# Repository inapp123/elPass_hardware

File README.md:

# ePass EL or elPass

**An open-source EL display controller built on the Xilinx Zynq-7010.**

ePass EL drives an electroluminescent (EL) panel from a Zynq-7010 SoC, pairing
PS-side Linux with PL-side panel timing so you get a real compositor on top of a
display technology that usually only sees bit-banged microcontroller drivers.
HDMI in/out, WiFi/BT, USB host, a resistive touchscreen, and USB-C PD power all
live on a single self-designed four-layer board.

> Rhodes Island Engineering Dept. (c) 1097 — *because every ruler needs a screen.*

---

## Status

| Subsystem            | State                                                        |
| -------------------- | ------------------------------------------------------------ |
| PCB (4-layer)        | **Fabricated and bring-up tested.** Working hardware.        |
| FPGA / Linux         | Architecture defined; EL driver + DRM compositor in progress |
| Enclosure            | 2-piece FDM/resin shell, parametric (build123d), in design   |

This is `Rev 1`. KiCad 10.0.3 source, schematic dated 2026-05-25.

PCB is designed for JLC04016-3313 stack.1.6mm,3313 imdepend matching.

---

## Highlights

- **Zynq-7010 (CLG400)** — dual-core Cortex-A9 PS + Artix-class PL on one die.
- **EL panel driver in the PL** — column/row drive (`UD*`/`LD*`/`CP*`/`S`) with
  1-bit temporal dithering, level-shifted to the panel through dual TXS0108E.
- **DRM/KMS on Linux** — a single-master compositor owns the CRTC; clients hand
  in buffers over dmabuf. Legacy fbdev programs and even an X server can run as
  clients without ever touching the real DRM master.
- **HDMI, both directions** — J2 is a dual-mode sink/source. Default build is a
  sink (TMDS receive into HR banks via IDELAY/ISERDES); populate `D2` to flip it
  into a source.
- **WiFi + Bluetooth** — RTL8723BS over SDIO (routed through EMIO to the PL),
  with a 2.4 GHz chip antenna and a proper RF keepout.
- **USB-C PD power** — CH224K negotiates 12 V for the panel rail; data lines
  stay free for whatever you want.
- **USB 2.0 host** — USB3320 ULPI PHY (24 MHz) to a full-size Type-A port.
- **Resistive touch** — XPT2046 over SPI.
- **microSD** boot + storage, RTC-less but with the usual JTAG/UART debug paths.

---

## Architecture

```mermaid
flowchart TB
    USBC[USB-C In<br/>CH224K PD sink] --> PWR
    PWR[EA3059 quad buck<br/>+ TPS563201] -->|1V0 / 1V8 / 1V35 / 3V3 / 5V / 12V| ZYNQ

    subgraph ZYNQ[Zynq-7010]
        PS[PS<br/>Cortex-A9 + Linux]
        PL[PL<br/>EL timing + dither<br/>HDMI TMDS]
    end

    PS <-->|EMIO SDIO| WIFI[RTL8723BS<br/>WiFi/BT]
    PS --> USB[USB3320 ULPI] --> USBA[USB-A Host]
    PS --> SD[microSD]
    PS <-->|DDR| DDR[MT41K256M16<br/>512 MB DDR3L]

    PL -->|level shift| EL[EL Panel]
    PL <--> HDMI[HDMI A<br/>sink / source]
    PS -->|SPI| TOUCH[XPT2046<br/>resistive touch]
```

### PS / PL split

- **PS** runs Linux and owns the slow-and-smart side: USB, SD, the RTL8723BS
  (SDIO bridged out through EMIO to PL pins), DDR3L, and the touch SPI link.
- **PL** owns the timing-critical side: generating EL panel drive waveforms with
  1-bit dithering, and the HDMI TMDS datapath.

---

## Power tree

USB-C comes in, CH224K trips the source to **12 V**, and everything fans out from
there. The Zynq rails are brought up in the order the datasheet asks for.

| Rail   | Source       | Notes                                  |
| ------ | ------------ | -------------------------------------- |
| +5 V   | TPS563201    | Buck from VBUS                         |
| +1.0 V | EA3059       | `VCCINT` / `VCCPINT`                    |
| +1.8 V | EA3059       | `VCCAUX` / `VCCPAUX` / MIO bank 1       |
| +1.35 V| EA3059       | DDR3L `VCCO_DDR`                        |
| +3.3 V | EA3059       | I/O banks, MIO bank 0, last to rise    |

**Sequence:** `1.0 V → 1.8 V → 1.35 V → 3.3 V`
(approx. instant → 22 ms → 41 ms → 55 ms, set by the enable-cap timing).
A **MAX811** supervises the last-rising 3.3 V rail and drives `PS_POR_B`.

**Panel budget:** 5 V @ 300 mA max, 12 V @ 1.3 A max.

---

## Boot configuration

Mode straps live on the MIO pins (see `zynq_misc`):

| Pins      | Value      | Meaning                                   |
| --------- | ---------- | ----------------------------------------- |
| MIO[6]    | `0`        | Wait for PLL lock, then run BootROM       |
| MIO[8:7]  | `2'b10`    | 3.3 V on both MIO banks                    |
| MIO[5:3]  | `3'b110`   | Boot from SD card                          |
| MIO[2]    | `0`        | JTAG chain: cascaded                       |

PS reference clock is a 50 MHz oscillator. JTAG is broken out on a ZX-SH1.0
header for bring-up.

---

## Software stack

The interesting part isn't that it runs Linux — it's *how the display is shared.*

- **Single-master DRM compositor.** A DRM lease can't split a CRTC between two
  masters, so one compositor owns all atomic commits. Clients submit buffers as
  dmabuf file descriptors passed over a Unix socket (`SCM_RIGHTS`).
- **Legacy fbdev support** via `LD_PRELOAD`, intercepting `open`/`ioctl`/`mmap`
  so old framebuffer programs think they own a screen.
- **X11 as a client** — `xf86-video-fbdev` runs against the compositor's virtual
  framebuffer, keeping the compositor as the sole DRM master.
- **Touch routing.** The real input device is grabbed (`EVIOCGRAB`) and a virtual
  device is published via `uinput`/`libevdev`; the compositor routes events by
  overlay visibility. On focus switch, in-flight multitouch slots are cancelled
  cleanly (`ABS_MT_TRACKING_ID = -1`, `BTN_TOUCH = 0`, `SYN_REPORT`). A udev rule
  (`LIBINPUT_IGNORE_DEVICE=1`) hides the raw device from X's libinput.

## Credits

This design stands on the shoulders of:

- **ZYNQ_Ruler** by Stanlazy — <https://github.com/Stanlazy/ZYNQ_Ruler>
- **Enchanter** by Modos Tech / Wenting Zhang
- **EBAZ4205** community reverse-engineering work

Thanks to everyone who documented Zynq-7010 minimal designs and EL driving so the
rest of us didn't have to start from a blank schematic.

---

## License

CERN-OHL-P.

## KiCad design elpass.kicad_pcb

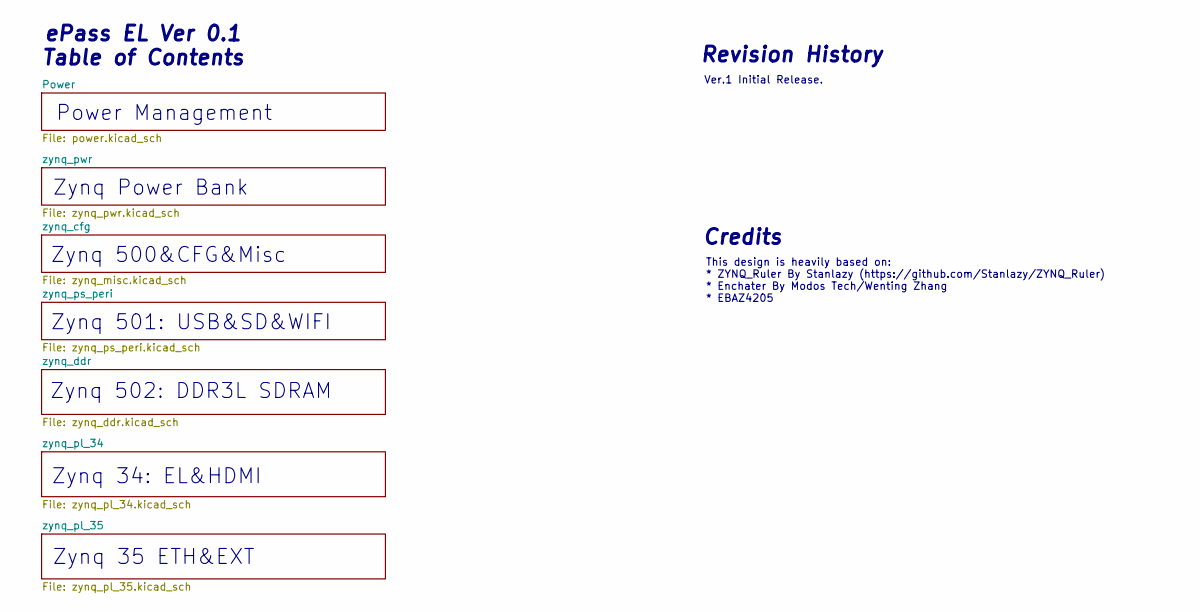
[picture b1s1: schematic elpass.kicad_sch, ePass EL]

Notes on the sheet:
Zynq Power Bank
Zynq 502: DDR3L SDRAM
Zynq 35 ETH&EXT
ePass EL Ver 0.1 Table of Contents
Power Management
Credits
Zynq 500&CFG&Misc
Zynq 34: EL&HDMI
Ver.1 Initial Release.
Zynq 501: USB&SD&WIFI
This design is heavily based on: * ZYNQ_Ruler By Stanlazy (https://github.com/Stanlazy/ZYNQ_Ruler) * Enchater By Modos Tech/Wenting Zhang * EBAZ4205
Revision History

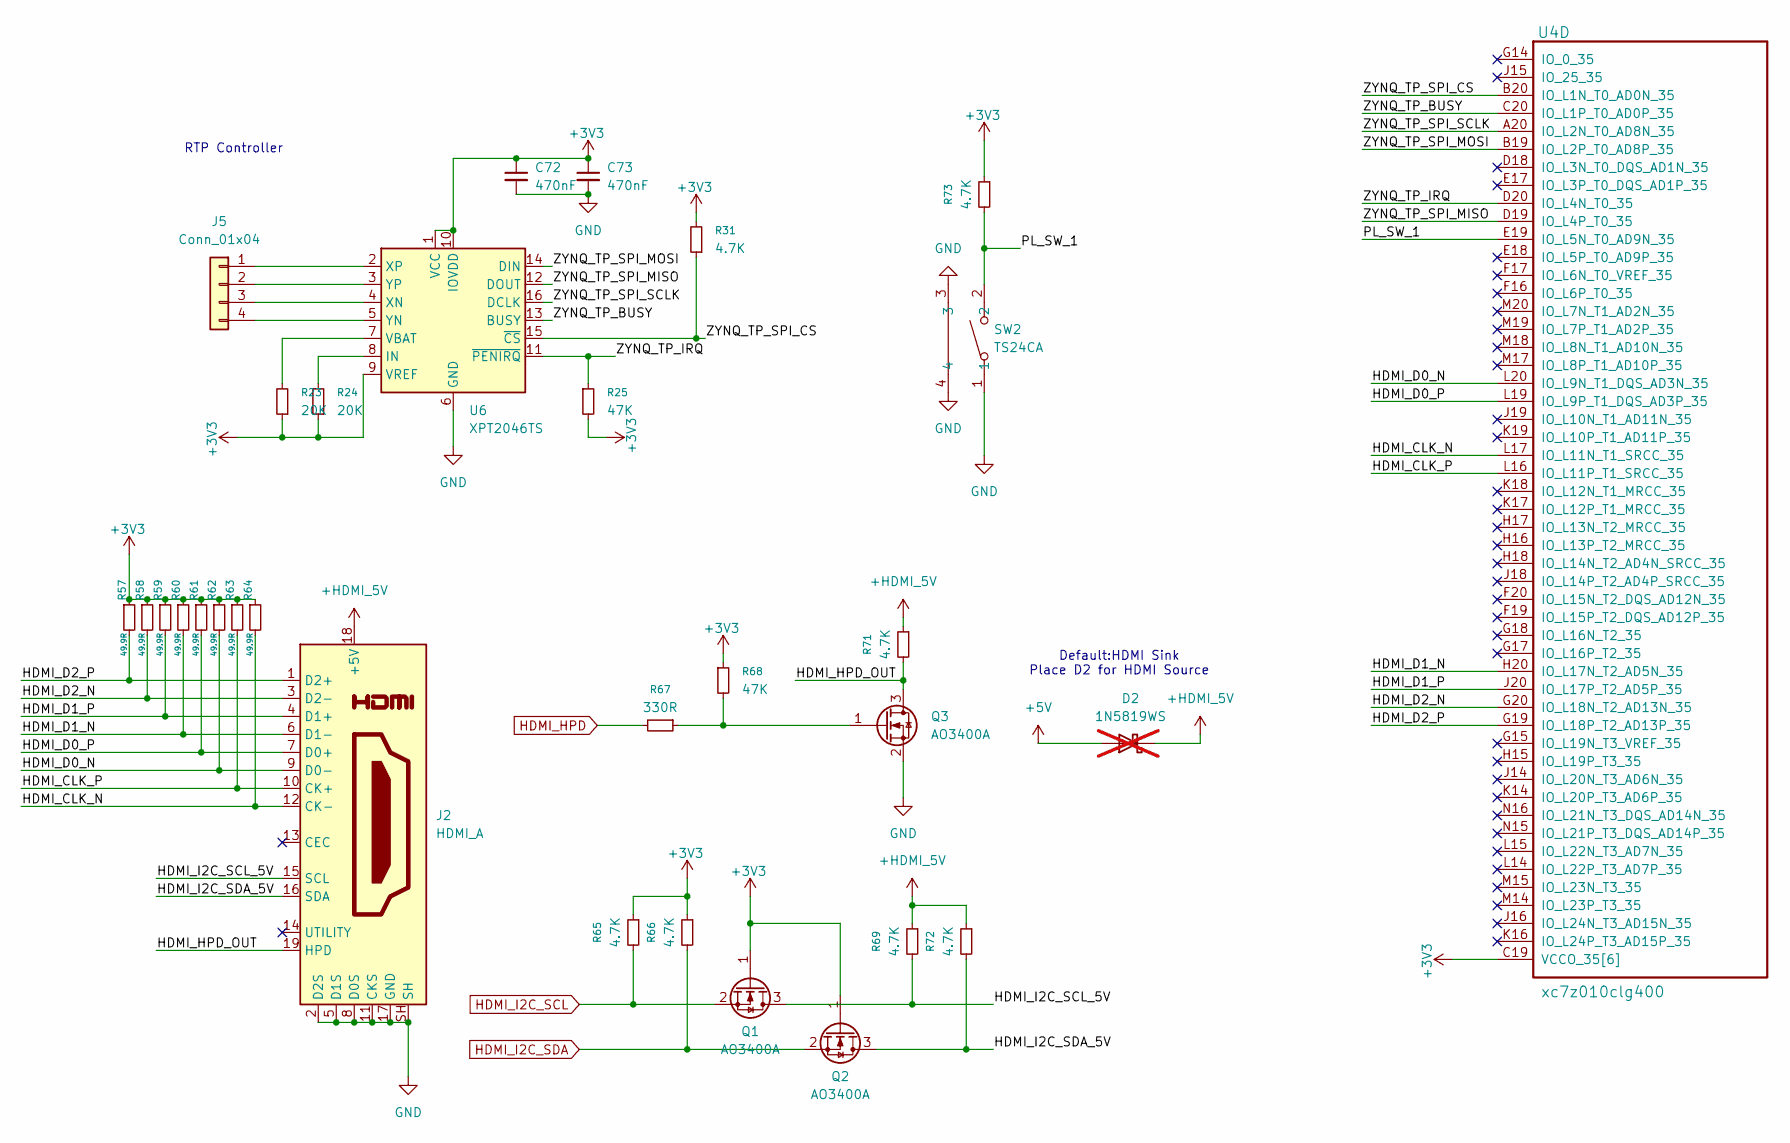
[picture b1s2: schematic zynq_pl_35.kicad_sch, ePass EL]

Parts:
C72, C73: 470nF; C_0201_0603Metric
D2: 1N5819WS; D_SOD-323; not fitted
J2: HDMI_A; HDMI_A_Molex_208658-1001_Horizontal
J5: Conn_01x04; PinHeader_1x04_P2.54mm_Horizontal
Q1, Q2, Q3: AO3400A; SOT-23
R23, R24: 20K; R_0402_1005Metric
R25, R68: 47K; R_0402_1005Metric
R31, R65, R66, R69, R71, R72, R73: 4.7K; R_0402_1005Metric
R57, R58, R59, R60, R61, R62, R63, R64: 49.9R; R_0402_1005Metric
R67: 330R; R_0402_1005Metric
SW2: TS24CA; SW-SMD_2P-TS24CA; MPN TS24CA; LCSC Part C393942
U4: xc7z010clg400; Xilinx_CLG400_NoPaste_JLC_Package_Delay
U6: XPT2046TS; TSSOP-16_4.4x5mm_P0.65mm

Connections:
+3V3: C72.1, C73.1, Q1.1 (G), Q2.1 (G), R23.1, R24.1, R25.2, R31.2, R57.1, R58.1, R59.1, R60.1, R61.1, R62.1, R63.1, R64.1, R65.1, R66.1, R68.1, R73.1, U4.C19 (VCCO_35[6]), U4.F18 (VCCO_35[6]), U4.H14 (VCCO_35[6]), U4.J17 (VCCO_35[6]), U4.K20 (VCCO_35[6]), U4.M16 (VCCO_35[6]), U6.1 (VCC), U6.9 (VREF), U6.10 (IOVDD); also elsewhere on the board
+5V: D2.2 (A); also elsewhere on the board
+HDMI_5V: D2.1 (K), J2.18 (+5V), R69.1, R71.1, R72.1
/zynq_pl_35/HDMI_CLK_N: J2.12 (CK-), R64.2, U4.L17 (IO_L11N_T1_SRCC_35)
/zynq_pl_35/HDMI_CLK_P: J2.10 (CK+), R63.2, U4.L16 (IO_L11P_T1_SRCC_35)
/zynq_pl_35/HDMI_D0_N: J2.9 (D0-), R62.2, U4.L20 (IO_L9N_T1_DQS_AD3N_35)
/zynq_pl_35/HDMI_D0_P: J2.7 (D0+), R61.2, U4.L19 (IO_L9P_T1_DQS_AD3P_35)
/zynq_pl_35/HDMI_D1_N: J2.6 (D1-), R60.2, U4.H20 (IO_L17N_T2_AD5N_35)
/zynq_pl_35/HDMI_D1_P: J2.4 (D1+), R59.2, U4.J20 (IO_L17P_T2_AD5P_35)
/zynq_pl_35/HDMI_D2_N: J2.3 (D2-), R58.2, U4.G20 (IO_L18N_T2_AD13N_35)
/zynq_pl_35/HDMI_D2_P: J2.1 (D2+), R57.2, U4.G19 (IO_L18P_T2_AD13P_35)
/zynq_pl_35/HDMI_HPD_OUT: J2.19 (HPD), Q3.3 (D), R71.2
/zynq_pl_35/HDMI_I2C_SCL_5V: J2.15 (SCL), Q1.3 (D), R69.2
/zynq_pl_35/HDMI_I2C_SDA_5V: J2.16 (SDA), Q2.3 (D), R72.2
/zynq_pl_35/PL_SW_1: R73.2, SW2.2, U4.E19 (IO_L5N_T0_AD9N_35)
/zynq_pl_35/ZYNQ_TP_BUSY: U4.C20 (IO_L1P_T0_AD0P_35), U6.13 (BUSY)
/zynq_pl_35/ZYNQ_TP_IRQ: R25.1, U4.D20 (IO_L4N_T0_35), U6.11 (~PENIRQ)
/zynq_pl_35/ZYNQ_TP_SPI_CS: R31.1, U4.B20 (IO_L1N_T0_AD0N_35), U6.15 (~CS)
/zynq_pl_35/ZYNQ_TP_SPI_MISO: U4.D19 (IO_L4P_T0_35), U6.12 (DOUT)
/zynq_pl_35/ZYNQ_TP_SPI_MOSI: U4.B19 (IO_L2P_T0_AD8P_35), U6.14 (DIN)
/zynq_pl_35/ZYNQ_TP_SPI_SCLK: U4.A20 (IO_L2N_T0_AD8N_35), U6.16 (DCLK)
GND: C72.2, C73.2, J2.2 (D2S), J2.5 (D1S), J2.8 (D0S), J2.11 (CKS), J2.17 (GND), J2.SH, Q3.2 (S), SW2.1, SW2.3, SW2.4, U6.6 (GND); also elsewhere on the board
HDMI_HPD: R67.2; also elsewhere on the board
HDMI_I2C_SCL: Q1.2 (S), R65.2; also elsewhere on the board
HDMI_I2C_SDA: Q2.2 (S), R66.2; also elsewhere on the board
unnamed: J5.1, U6.2 (XP)
unnamed: J5.2, U6.3 (YP)
unnamed: J5.3, U6.4 (XN)
unnamed: J5.4, U6.5 (YN)
unnamed: Q3.1 (G), R67.1, R68.2
unnamed: R24.2, U6.8 (IN)
unnamed: R23.2, U6.7 (VBAT)

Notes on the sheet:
Default:HDMI Sink Place D2 for HDMI Source
RTP Controller

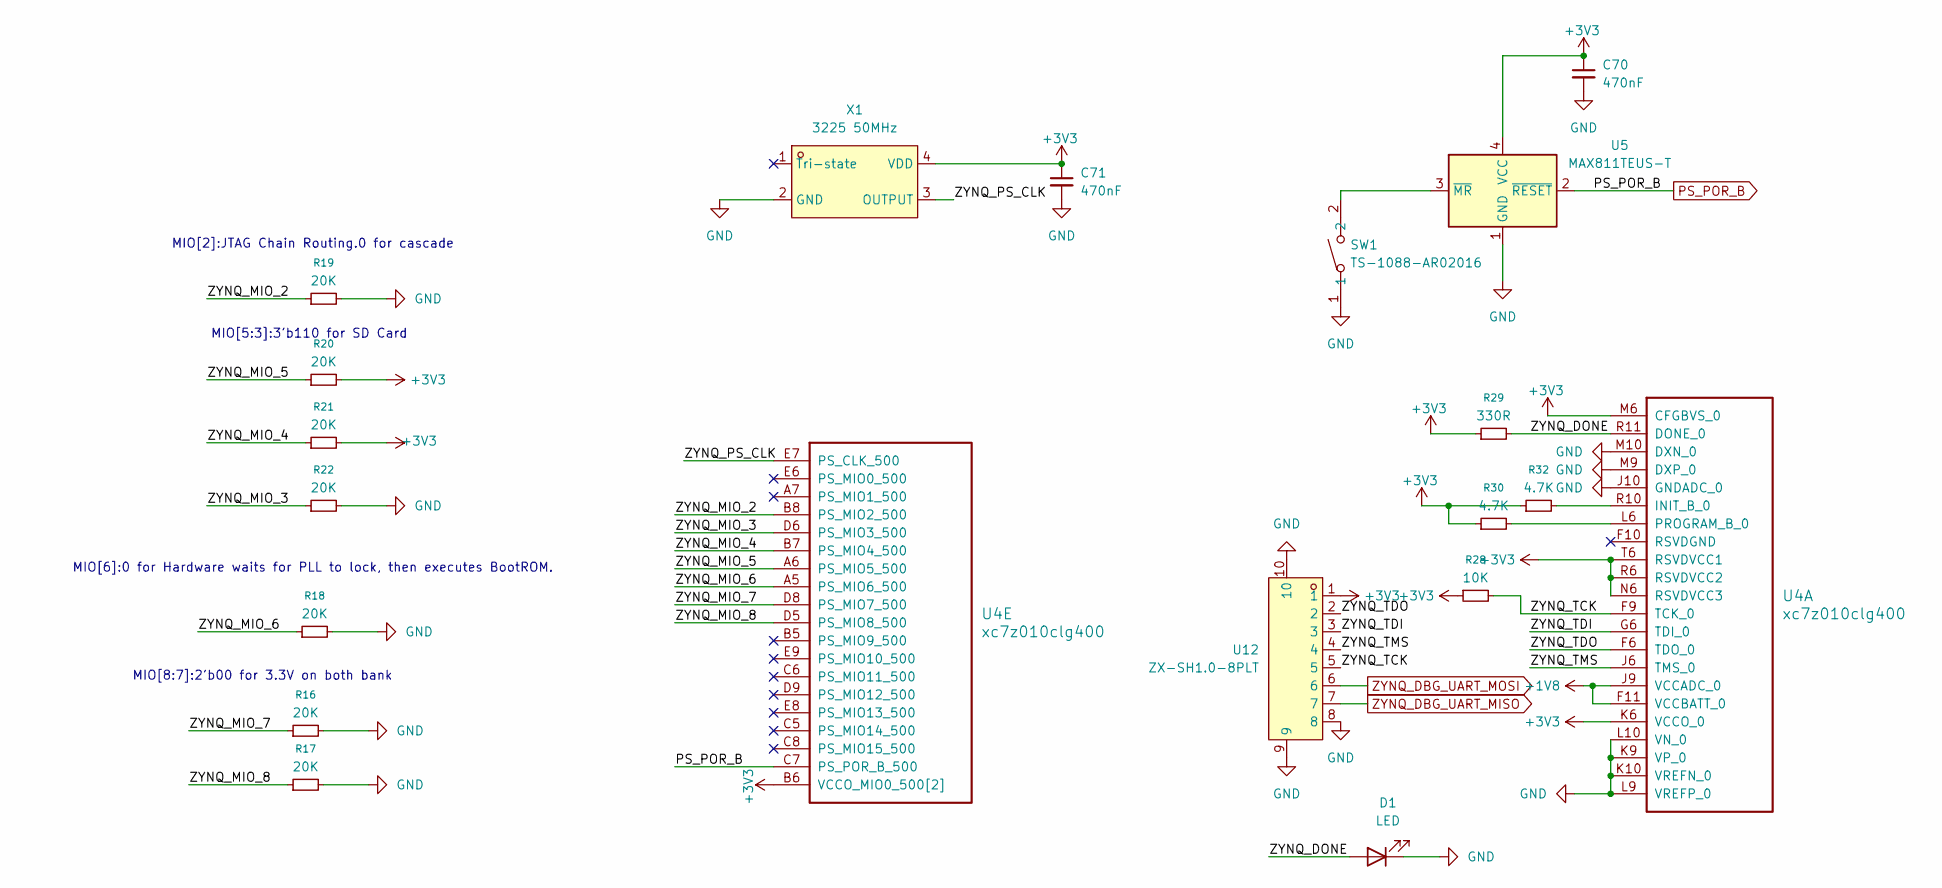
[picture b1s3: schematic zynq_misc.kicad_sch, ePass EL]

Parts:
C70, C71: 470nF; C_0201_0603Metric
D1: LED; LED_0603_1608Metric
R16, R17, R18, R19, R20, R21, R22: 20K; R_0402_1005Metric
R28: 10K; R_0402_1005Metric
R29: 330R; R_0402_1005Metric
R30, R32: 4.7K; R_0402_1005Metric
SW1: TS-1088-AR02016; SW-SMD_L3.9-W3.0-P4.45; MPN TS-1088-AR02016; LCSC Part C720477
U4: xc7z010clg400; Xilinx_CLG400_NoPaste_JLC_Package_Delay
U5: MAX811TEUS-T; SOT-143
U12: ZX-SH1.0-8PLT; CONN-SMD_8P-P1.00_MEGASTAR_ZX-SH1.0-8PLT; MPN ZX-SH1.0-8PLT; LCSC Part C7430457
X1: 3225 50MHz; OSC-SMD_4P-L3.2-W2.5-BL; MPN OT322550MJBA4SL; LCSC Part C717684

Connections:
+1V8: U4.F11 (VCCBATT_0), U4.J9 (VCCADC_0); also elsewhere on the board
+3V3: C70.1, C71.1, R20.2, R21.2, R28.1, R29.1, R30.1, R32.1, U4.B6 (VCCO_MIO0_500[2]), U4.D7 (VCCO_MIO0_500[2]), U4.K6 (VCCO_0), U4.M6 (CFGBVS_0), U4.N6 (RSVDVCC3), U4.R6 (RSVDVCC2), U4.T6 (RSVDVCC1), U5.4 (VCC), U12.1, X1.4 (VDD); also elsewhere on the board
/zynq_cfg/ZYNQ_DONE: D1.2 (A), R29.2, U4.R11 (DONE_0)
/zynq_cfg/ZYNQ_MIO_2: R19.1, U4.B8 (PS_MIO2_500)
/zynq_cfg/ZYNQ_MIO_3: R22.1, U4.D6 (PS_MIO3_500)
/zynq_cfg/ZYNQ_MIO_4: R21.1, U4.B7 (PS_MIO4_500)
/zynq_cfg/ZYNQ_MIO_5: R20.1, U4.A6 (PS_MIO5_500)
/zynq_cfg/ZYNQ_MIO_6: R18.1, U4.A5 (PS_MIO6_500)
/zynq_cfg/ZYNQ_MIO_7: R16.1, U4.D8 (PS_MIO7_500)
/zynq_cfg/ZYNQ_MIO_8: R17.1, U4.D5 (PS_MIO8_500)
/zynq_cfg/ZYNQ_PS_CLK: U4.E7 (PS_CLK_500), X1.3 (OUTPUT)
/zynq_cfg/ZYNQ_TCK: R28.2, U4.F9 (TCK_0), U12.5
/zynq_cfg/ZYNQ_TDI: U4.G6 (TDI_0), U12.3
/zynq_cfg/ZYNQ_TDO: U4.F6 (TDO_0), U12.2
/zynq_cfg/ZYNQ_TMS: U4.J6 (TMS_0), U12.4
GND: C70.2, C71.2, D1.1 (K), R16.2, R17.2, R18.2, R19.2, R22.2, SW1.1, U4.J10 (GNDADC_0), U4.K9 (VP_0), U4.K10 (VREFN_0), U4.L9 (VREFP_0), U4.L10 (VN_0), U4.M9 (DXP_0), U4.M10 (DXN_0), U5.1 (GND), U12.8, U12.9, U12.10, X1.2 (GND); also elsewhere on the board
unnamed: R32.2, U4.R10 (INIT_B_0)
unnamed: R30.2, U4.L6 (PROGRAM_B_0)
unnamed: SW1.2, U5.3 (~MR)
PS_POR_B: U4.C7 (PS_POR_B_500), U5.2 (~RESET)
ZYNQ_DBG_UART_MISO: U12.7; also elsewhere on the board
ZYNQ_DBG_UART_MOSI: U12.6; also elsewhere on the board

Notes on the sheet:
MIO[5:3]:3'b110 for SD Card
MIO[8:7]:2'b00 for 3.3V on both bank
MIO[2]:JTAG Chain Routing.0 for cascade
MIO[6]:0 for Hardware waits for PLL to lock, then executes BootROM.

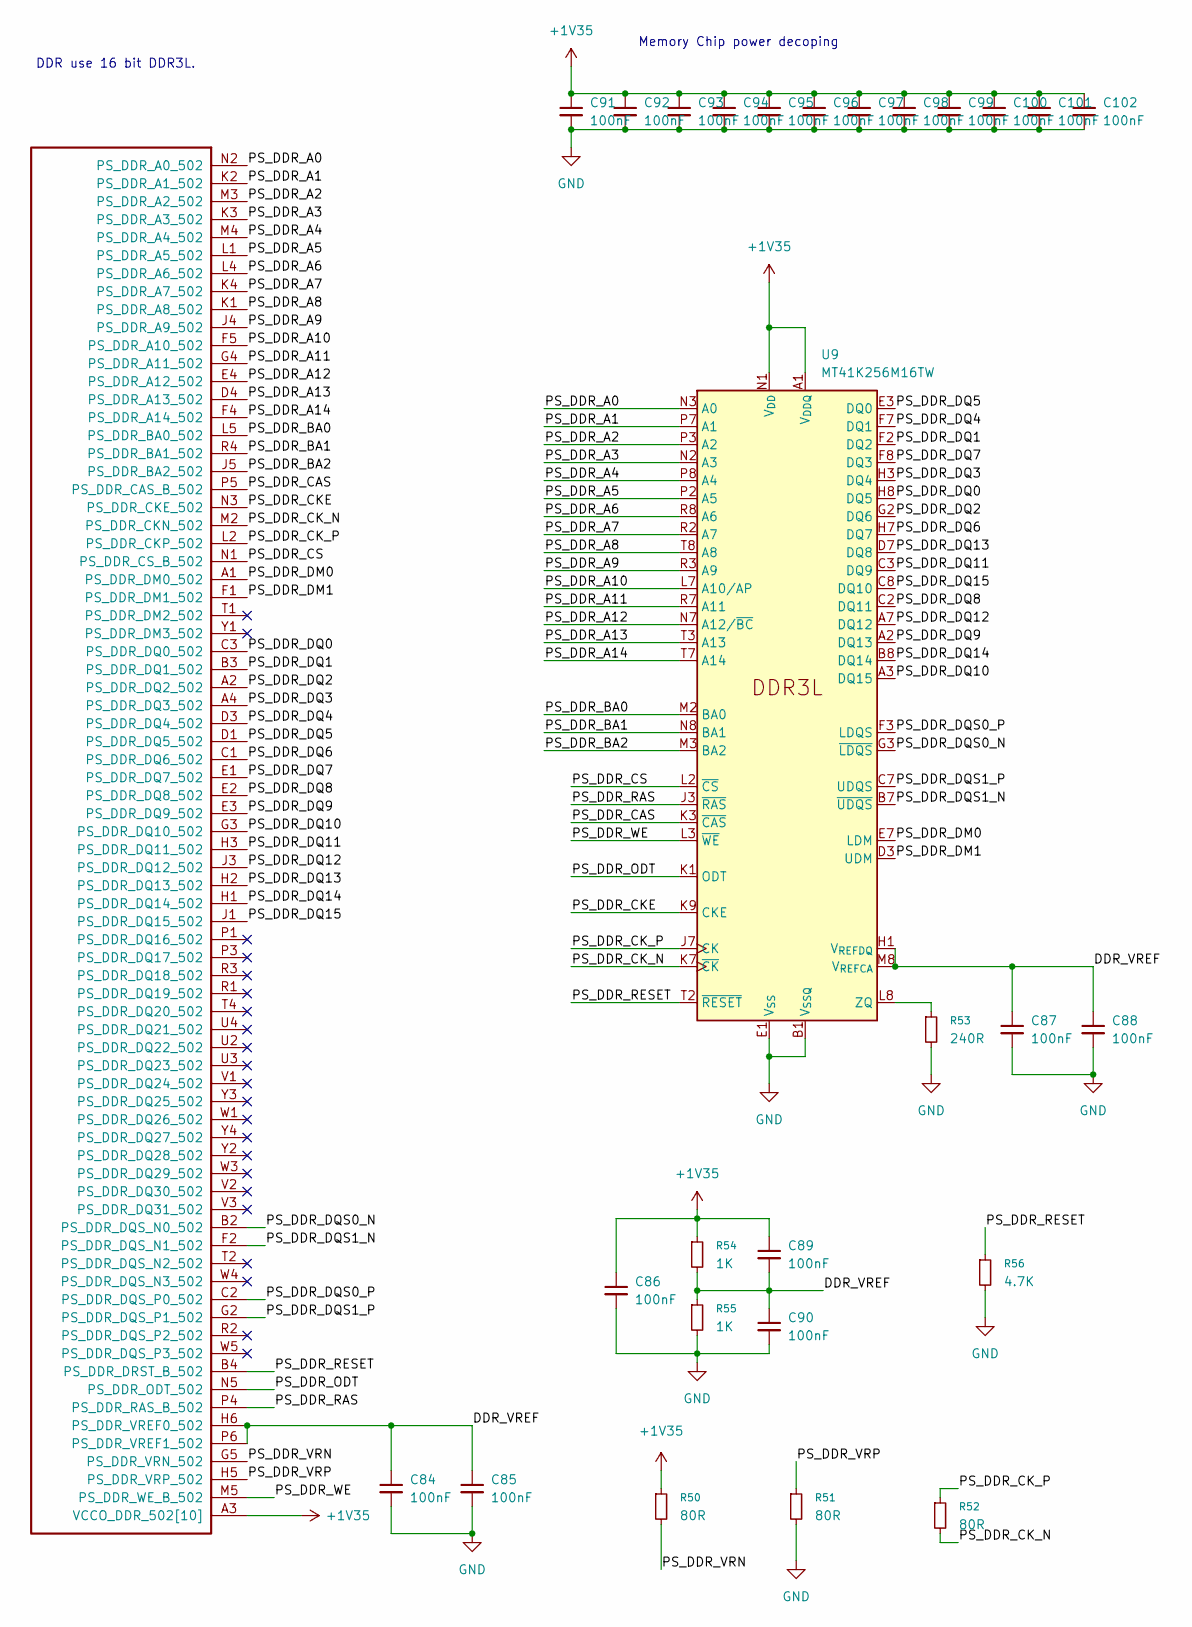
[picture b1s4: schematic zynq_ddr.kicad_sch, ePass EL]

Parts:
C84, C86, C87, C88, C89, C90, C91, C92, C93, C94, C95, C98, C99, C100, C101, C102: 100nF; C_0201_0603Metric
C85, C96, C97: 100nF; C_0201_0603Metric_WideGap
R50, R51: 80R; R_0201_0603Metric
R52: 80R; C_0201_0603Metric_WideGap
R53: 240R; R_0201_0603Metric
R54, R55: 1K; R_0402_1005Metric
R56: 4.7K; R_0402_1005Metric
U4: xc7z010clg400; Xilinx_CLG400_NoPaste_JLC_Package_Delay
U9: MT41K256M16TW; BGA-96_P0.8mm_NoPaste

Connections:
+1V35: C86.1, C89.1, C91.1, C92.1, C93.1, C94.1, C95.1, C96.1, C97.1, C98.1, C99.1, C100.1, C101.1, C102.1, R50.1, R54.1, U4.A3 (VCCO_DDR_502[10]), U4.D2 (VCCO_DDR_502[10]), U4.E5 (VCCO_DDR_502[10]), U4.G1 (VCCO_DDR_502[10]), U4.H4 (VCCO_DDR_502[10]), U4.L3 (VCCO_DDR_502[10]), U4.P2 (VCCO_DDR_502[10]), U4.R5 (VCCO_DDR_502[10]), U4.U1 (VCCO_DDR_502[10]), U4.V4 (VCCO_DDR_502[10]), U9.A1 (V_{DDQ}), U9.A8 (V_{DDQ}), U9.B2 (V_{DD}), U9.C1 (V_{DDQ}), U9.C9 (V_{DDQ}), U9.D2 (V_{DDQ}), U9.D9 (V_{DD}), U9.E9 (V_{DDQ}), U9.F1 (V_{DDQ}), U9.G7 (V_{DD}), U9.H2 (V_{DDQ}), U9.H9 (V_{DDQ}), U9.K2 (V_{DD}), U9.K8 (V_{DD}), U9.N1 (V_{DD}), U9.N9 (V_{DD}), U9.R1 (V_{DD}), U9.R9 (V_{DD}); also elsewhere on the board
/zynq_ddr/DDR_VREF: C84.1, C85.1, C87.1, C88.1, C89.2, C90.1, R54.2, R55.1, U4.H6 (PS_DDR_VREF0_502), U4.P6 (PS_DDR_VREF1_502), U9.H1 (V_{REFDQ}), U9.M8 (V_{REFCA})
/zynq_ddr/PS_DDR_A0: U4.N2 (PS_DDR_A0_502), U9.N3 (A0)
/zynq_ddr/PS_DDR_A1: U4.K2 (PS_DDR_A1_502), U9.P7 (A1)
/zynq_ddr/PS_DDR_A2: U4.M3 (PS_DDR_A2_502), U9.P3 (A2)
/zynq_ddr/PS_DDR_A3: U4.K3 (PS_DDR_A3_502), U9.N2 (A3)
/zynq_ddr/PS_DDR_A4: U4.M4 (PS_DDR_A4_502), U9.P8 (A4)
/zynq_ddr/PS_DDR_A5: U4.L1 (PS_DDR_A5_502), U9.P2 (A5)
/zynq_ddr/PS_DDR_A6: U4.L4 (PS_DDR_A6_502), U9.R8 (A6)
/zynq_ddr/PS_DDR_A7: U4.K4 (PS_DDR_A7_502), U9.R2 (A7)
/zynq_ddr/PS_DDR_A8: U4.K1 (PS_DDR_A8_502), U9.T8 (A8)
/zynq_ddr/PS_DDR_A9: U4.J4 (PS_DDR_A9_502), U9.R3 (A9)
/zynq_ddr/PS_DDR_A10: U4.F5 (PS_DDR_A10_502), U9.L7 (A10/AP)
/zynq_ddr/PS_DDR_A11: U4.G4 (PS_DDR_A11_502), U9.R7 (A11)
/zynq_ddr/PS_DDR_A12: U4.E4 (PS_DDR_A12_502), U9.N7 (A12/~BC)
/zynq_ddr/PS_DDR_A13: U4.D4 (PS_DDR_A13_502), U9.T3 (A13)
/zynq_ddr/PS_DDR_A14: U4.F4 (PS_DDR_A14_502), U9.T7 (A14)
/zynq_ddr/PS_DDR_BA0: U4.L5 (PS_DDR_BA0_502), U9.M2 (BA0)
/zynq_ddr/PS_DDR_BA1: U4.R4 (PS_DDR_BA1_502), U9.N8 (BA1)
/zynq_ddr/PS_DDR_BA2: U4.J5 (PS_DDR_BA2_502), U9.M3 (BA2)
/zynq_ddr/PS_DDR_CAS: U4.P5 (PS_DDR_CAS_B_502), U9.K3 (~CAS)
/zynq_ddr/PS_DDR_CKE: U4.N3 (PS_DDR_CKE_502), U9.K9 (CKE)
/zynq_ddr/PS_DDR_CK_N: R52.2, U4.M2 (PS_DDR_CKN_502), U9.K7 (~CK)
/zynq_ddr/PS_DDR_CK_P: R52.1, U4.L2 (PS_DDR_CKP_502), U9.J7 (CK)
/zynq_ddr/PS_DDR_CS: U4.N1 (PS_DDR_CS_B_502), U9.L2 (~CS)
/zynq_ddr/PS_DDR_DM0: U4.A1 (PS_DDR_DM0_502), U9.E7 (LDM)
/zynq_ddr/PS_DDR_DM1: U4.F1 (PS_DDR_DM1_502), U9.D3 (UDM)
/zynq_ddr/PS_DDR_DQ0: U4.C3 (PS_DDR_DQ0_502), U9.H8 (DQ5)
/zynq_ddr/PS_DDR_DQ1: U4.B3 (PS_DDR_DQ1_502), U9.F2 (DQ2)
/zynq_ddr/PS_DDR_DQ2: U4.A2 (PS_DDR_DQ2_502), U9.G2 (DQ6)
/zynq_ddr/PS_DDR_DQ3: U4.A4 (PS_DDR_DQ3_502), U9.H3 (DQ4)
/zynq_ddr/PS_DDR_DQ4: U4.D3 (PS_DDR_DQ4_502), U9.F7 (DQ1)
/zynq_ddr/PS_DDR_DQ5: U4.D1 (PS_DDR_DQ5_502), U9.E3 (DQ0)
/zynq_ddr/PS_DDR_DQ6: U4.C1 (PS_DDR_DQ6_502), U9.H7 (DQ7)
/zynq_ddr/PS_DDR_DQ7: U4.E1 (PS_DDR_DQ7_502), U9.F8 (DQ3)
/zynq_ddr/PS_DDR_DQ8: U4.E2 (PS_DDR_DQ8_502), U9.C2 (DQ11)
/zynq_ddr/PS_DDR_DQ9: U4.E3 (PS_DDR_DQ9_502), U9.A2 (DQ13)
/zynq_ddr/PS_DDR_DQ10: U4.G3 (PS_DDR_DQ10_502), U9.A3 (DQ15)
/zynq_ddr/PS_DDR_DQ11: U4.H3 (PS_DDR_DQ11_502), U9.C3 (DQ9)
/zynq_ddr/PS_DDR_DQ12: U4.J3 (PS_DDR_DQ12_502), U9.A7 (DQ12)
/zynq_ddr/PS_DDR_DQ13: U4.H2 (PS_DDR_DQ13_502), U9.D7 (DQ8)
/zynq_ddr/PS_DDR_DQ14: U4.H1 (PS_DDR_DQ14_502), U9.B8 (DQ14)
/zynq_ddr/PS_DDR_DQ15: U4.J1 (PS_DDR_DQ15_502), U9.C8 (DQ10)
/zynq_ddr/PS_DDR_DQS0_N: U4.B2 (PS_DDR_DQS_N0_502), U9.G3 (~LDQS)
/zynq_ddr/PS_DDR_DQS0_P: U4.C2 (PS_DDR_DQS_P0_502), U9.F3 (LDQS)
/zynq_ddr/PS_DDR_DQS1_N: U4.F2 (PS_DDR_DQS_N1_502), U9.B7 (~UDQS)
/zynq_ddr/PS_DDR_DQS1_P: U4.G2 (PS_DDR_DQS_P1_502), U9.C7 (UDQS)
/zynq_ddr/PS_DDR_ODT: U4.N5 (PS_DDR_ODT_502), U9.K1 (ODT)
/zynq_ddr/PS_DDR_RAS: U4.P4 (PS_DDR_RAS_B_502), U9.J3 (~RAS)
/zynq_ddr/PS_DDR_RESET: R56.1, U4.B4 (PS_DDR_DRST_B_502), U9.T2 (~RESET)
/zynq_ddr/PS_DDR_VRN: R50.2, U4.G5 (PS_DDR_VRN_502)
/zynq_ddr/PS_DDR_VRP: R51.1, U4.H5 (PS_DDR_VRP_502)
/zynq_ddr/PS_DDR_WE: U4.M5 (PS_DDR_WE_B_502), U9.L3 (~WE)
GND: C84.2, C85.2, C86.2, C87.2, C88.2, C90.2, C91.2, C92.2, C93.2, C94.2, C95.2, C96.2, C97.2, C98.2, C99.2, C100.2, C101.2, C102.2, R51.2, R53.2, R55.2, R56.2, U9.A9 (V_{SS}), U9.B1 (V_{SSQ}), U9.B3 (V_{SS}), U9.B9 (V_{SSQ}), U9.D1 (V_{SSQ}), U9.D8 (V_{SSQ}), U9.E1 (V_{SS}), U9.E2 (V_{SSQ}), U9.E8 (V_{SSQ}), U9.F9 (V_{SSQ}), U9.G1 (V_{SSQ}), U9.G8 (V_{SS}), U9.G9 (V_{SSQ}), U9.J2 (V_{SS}), U9.J8 (V_{SS}), U9.M1 (V_{SS}), U9.M9 (V_{SS}), U9.P1 (V_{SS}), U9.P9 (V_{SS}), U9.T1 (V_{SS}), U9.T9 (V_{SS}); also elsewhere on the board
unnamed: R53.1, U9.L8 (ZQ)

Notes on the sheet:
DDR use 16 bit DDR3L.
Memory Chip power decoping

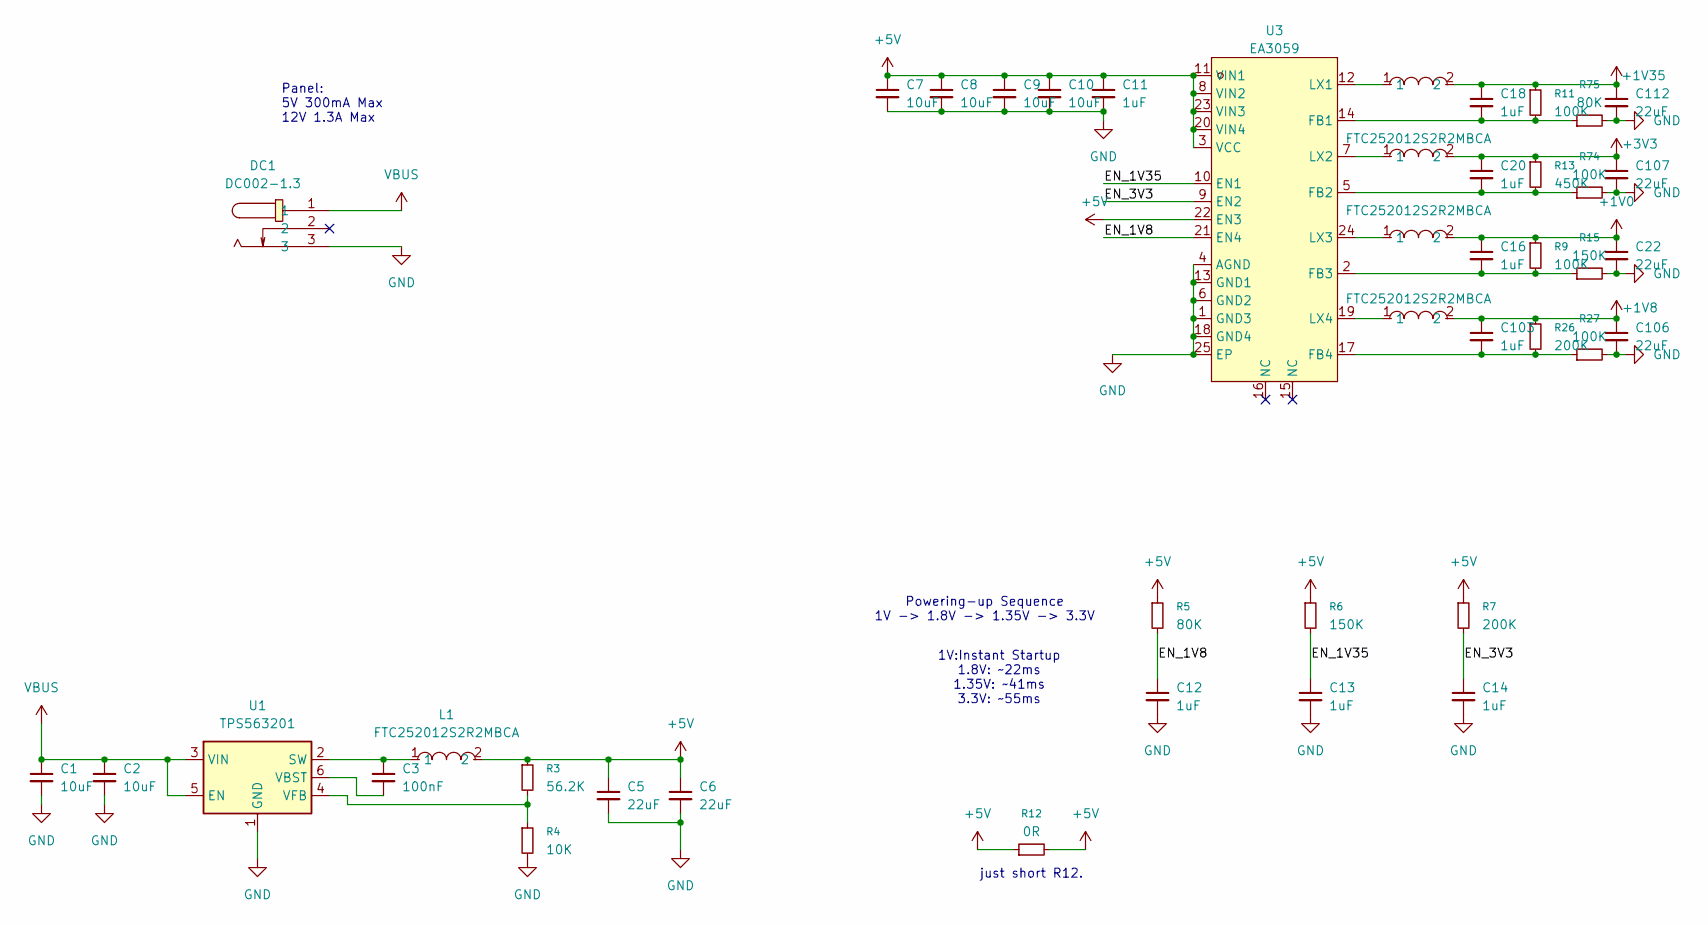
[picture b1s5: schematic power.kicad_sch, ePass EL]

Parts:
C1, C2, C7, C8, C9, C10: 10uF; C_0805_2012Metric
C3: 100nF; C_0201_0603Metric
C5, C6, C22, C106, C107, C112: 22uF; C_0603_1608Metric
C11, C12, C13, C14, C16, C18, C20, C103: 1uF; C_0402_1005Metric
DC1: DC002-1.3; DC-IN-TH_DC002-1.3; MPN DC002-1.3; LCSC Part C668593
L1, L3, L5, L6, L8: FTC252012S2R2MBCA; IND-SMD_L2.5-W2.0_MHCHL2520; MPN FTC252012S2R2MBCA; LCSC Part C5832372
R3: 56.2K; R_0402_1005Metric
R4: 10K; R_0402_1005Metric
R5, R75: 80K; R_0402_1005Metric
R6, R15: 150K; R_0402_1005Metric
R7, R26: 200K; R_0402_1005Metric
R9, R11, R27, R74: 100K; R_0402_1005Metric
R12: 0R; R_0805_2012Metric
R13: 450K; R_0402_1005Metric
U1: TPS563201; SOT-23-6
U3: EA3059; VQFN-24_L4.0-W4.0-P0.50-TL-EP2.5; MPN EA3059QDR; LCSC Part C111586

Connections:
+1V0: C16.1, C22.1, L3.2, R9.1; also elsewhere on the board
+1V8: C103.1, C106.1, L6.2, R26.1; also elsewhere on the board
+1V35: C18.1, C112.1, L5.2, R11.1; also elsewhere on the board
+3V3: C20.1, C107.1, L8.2, R13.1; also elsewhere on the board
+5V: C5.1, C6.1, C7.1, C8.1, C9.1, C10.1, C11.1, L1.2, R3.1, R5.1, R6.1, R7.1, R12.1, R12.2, U3.3 (VCC), U3.8 (VIN2), U3.11 (VIN1), U3.20 (VIN4), U3.22 (EN3), U3.23 (VIN3); also elsewhere on the board
/Power/EN_1V8: C12.1, R5.2, U3.21 (EN4)
/Power/EN_1V35: C13.1, R6.2, U3.10 (EN1)
/Power/EN_3V3: C14.1, R7.2, U3.9 (EN2)
GND: C1.2, C2.2, C5.2, C6.2, C7.2, C8.2, C9.2, C10.2, C11.2, C12.2, C13.2, C14.2, C22.2, C106.2, C107.2, C112.2, DC1.3, R4.2, R15.2, R27.2, R74.2, R75.2, U1.1 (GND), U3.1 (GND3), U3.4 (AGND), U3.6 (GND2), U3.13 (GND1), U3.18 (GND4), U3.25 (EP); also elsewhere on the board
unnamed: C3.1, L1.1, U1.2 (SW)
unnamed: C3.2, U1.6 (VBST)
unnamed: R3.2, R4.1, U1.4 (VFB)
unnamed: C18.2, R11.2, R75.1, U3.14 (FB1)
unnamed: C20.2, R13.2, R74.1, U3.5 (FB2)
unnamed: C16.2, R9.2, R15.1, U3.2 (FB3)
unnamed: C103.2, R26.2, R27.1, U3.17 (FB4)
unnamed: L5.1, U3.12 (LX1)
unnamed: L8.1, U3.7 (LX2)
unnamed: L3.1, U3.24 (LX3)
unnamed: L6.1, U3.19 (LX4)
VBUS: C1.1, C2.1, DC1.1, U1.3 (VIN), U1.5 (EN); also elsewhere on the board

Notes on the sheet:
Panel: 5V 300mA Max 12V 1.3A Max
just short R12.
Powering-up Sequence 1V -> 1.8V -> 1.35V -> 3.3V
1V:Instant Startup 1.8V: ~22ms 1.35V: ~41ms 3.3V: ~55ms

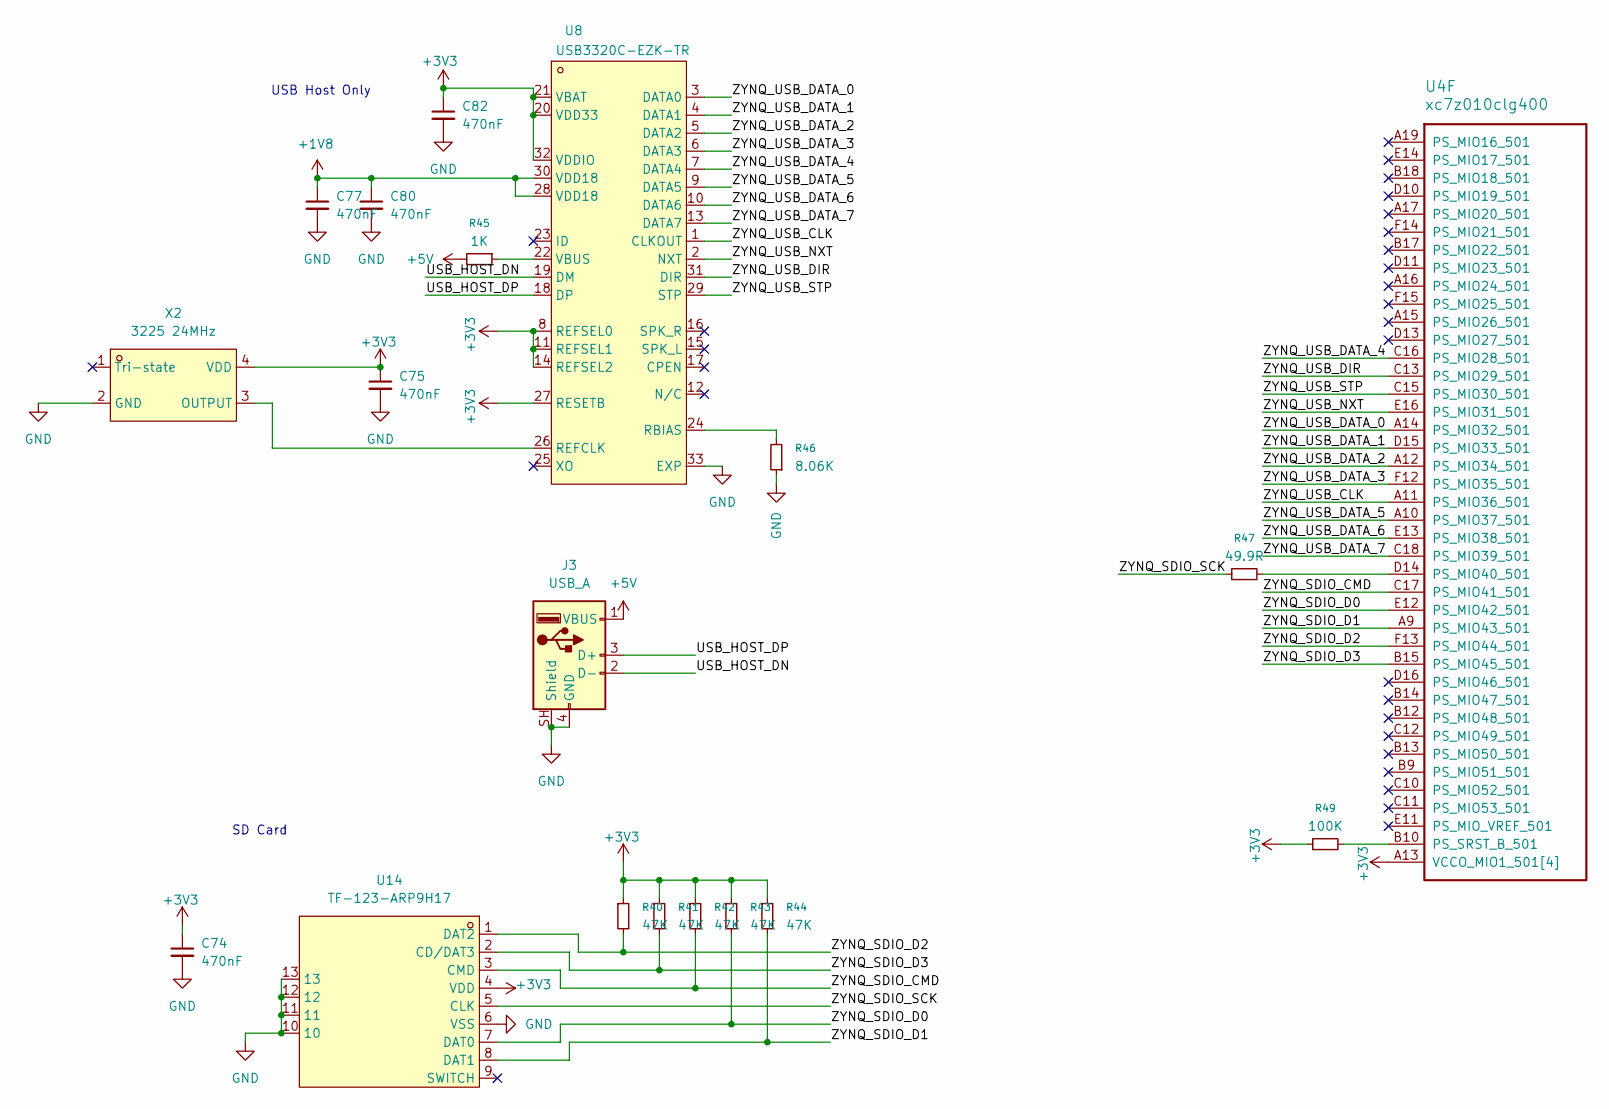
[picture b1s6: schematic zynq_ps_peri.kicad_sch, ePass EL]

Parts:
C74, C75, C77, C80, C82: 470nF; C_0201_0603Metric
J3: USB_A; USB_A_Molex_67643_Horizontal
R40, R41, R42, R43, R44: 47K; R_0402_1005Metric
R45: 1K; R_0402_1005Metric
R46: 8.06K; R_0402_1005Metric
R47: 49.9R; R_0402_1005Metric
R49: 100K; R_0402_1005Metric
U4: xc7z010clg400; Xilinx_CLG400_NoPaste_JLC_Package_Delay
U8: USB3320C-EZK-TR; QFN-32_L5.0-W5.0-P0.50-BL-EP3.4; MPN USB3320C-EZK-TR; LCSC Part C132156
U14: TF-123-ARP9H17; TF-SMD_TF-123-ARP9H15; MPN TF-123-ARP9H17; LCSC Part C2982548
X2: 3225 24MHz; OSC-SMD_4P-L3.2-W2.5-BL; MPN OT322550MJBA4SL; LCSC Part C717684

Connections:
+1V8: C77.1, C80.1, U8.28 (VDD18), U8.30 (VDD18); also elsewhere on the board
+3V3: C74.1, C75.1, C82.1, R40.1, R41.1, R42.1, R43.1, R44.1, R49.1, U4.A13 (VCCO_MIO1_501[4]), U4.B16 (VCCO_MIO1_501[4]), U4.D12 (VCCO_MIO1_501[4]), U4.E15 (VCCO_MIO1_501[4]), U8.8 (REFSEL0), U8.11 (REFSEL1), U8.14 (REFSEL2), U8.20 (VDD33), U8.21 (VBAT), U8.27 (RESETB), U8.32 (VDDIO), U14.4 (VDD), X2.4 (VDD); also elsewhere on the board
+5V: J3.1 (VBUS), R45.2; also elsewhere on the board
/zynq_ps_peri/USB_HOST_DN: J3.2 (D-), U8.19 (DM)
/zynq_ps_peri/USB_HOST_DP: J3.3 (D+), U8.18 (DP)
/zynq_ps_peri/ZYNQ_SDIO_CMD: R42.2, U4.C17 (PS_MIO41_501), U14.3 (CMD)
/zynq_ps_peri/ZYNQ_SDIO_D0: R43.2, U4.E12 (PS_MIO42_501), U14.7 (DAT0)
/zynq_ps_peri/ZYNQ_SDIO_D1: R44.2, U4.A9 (PS_MIO43_501), U14.8 (DAT1)
/zynq_ps_peri/ZYNQ_SDIO_D2: R40.2, U4.F13 (PS_MIO44_501), U14.1 (DAT2)
/zynq_ps_peri/ZYNQ_SDIO_D3: R41.2, U4.B15 (PS_MIO45_501), U14.2 (CD/DAT3)
/zynq_ps_peri/ZYNQ_SDIO_SCK: R47.1, U14.5 (CLK)
/zynq_ps_peri/ZYNQ_USB_CLK: U4.A11 (PS_MIO36_501), U8.1 (CLKOUT)
/zynq_ps_peri/ZYNQ_USB_DATA_0: U4.A14 (PS_MIO32_501), U8.3 (DATA0)
/zynq_ps_peri/ZYNQ_USB_DATA_1: U4.D15 (PS_MIO33_501), U8.4 (DATA1)
/zynq_ps_peri/ZYNQ_USB_DATA_2: U4.A12 (PS_MIO34_501), U8.5 (DATA2)
/zynq_ps_peri/ZYNQ_USB_DATA_3: U4.F12 (PS_MIO35_501), U8.6 (DATA3)
/zynq_ps_peri/ZYNQ_USB_DATA_4: U4.C16 (PS_MIO28_501), U8.7 (DATA4)
/zynq_ps_peri/ZYNQ_USB_DATA_5: U4.A10 (PS_MIO37_501), U8.9 (DATA5)
/zynq_ps_peri/ZYNQ_USB_DATA_6: U4.E13 (PS_MIO38_501), U8.10 (DATA6)
/zynq_ps_peri/ZYNQ_USB_DATA_7: U4.C18 (PS_MIO39_501), U8.13 (DATA7)
/zynq_ps_peri/ZYNQ_USB_DIR: U4.C13 (PS_MIO29_501), U8.31 (DIR)
/zynq_ps_peri/ZYNQ_USB_NXT: U4.E16 (PS_MIO31_501), U8.2 (NXT)
/zynq_ps_peri/ZYNQ_USB_STP: U4.C15 (PS_MIO30_501), U8.29 (STP)
GND: C74.2, C75.2, C77.2, C80.2, C82.2, J3.4 (GND), J3.SH (Shield), R46.1, U8.33 (EXP), U14.6 (VSS), U14.10, U14.11, U14.12, U14.13, X2.2 (GND); also elsewhere on the board
unnamed: R47.2, U4.D14 (PS_MIO40_501)
unnamed: R49.2, U4.B10 (PS_SRST_B_501)
unnamed: R46.2, U8.24 (RBIAS)
unnamed: U8.26 (REFCLK), X2.3 (OUTPUT)
unnamed: R45.1, U8.22 (VBUS)

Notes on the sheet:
USB Host Only
SD Card
